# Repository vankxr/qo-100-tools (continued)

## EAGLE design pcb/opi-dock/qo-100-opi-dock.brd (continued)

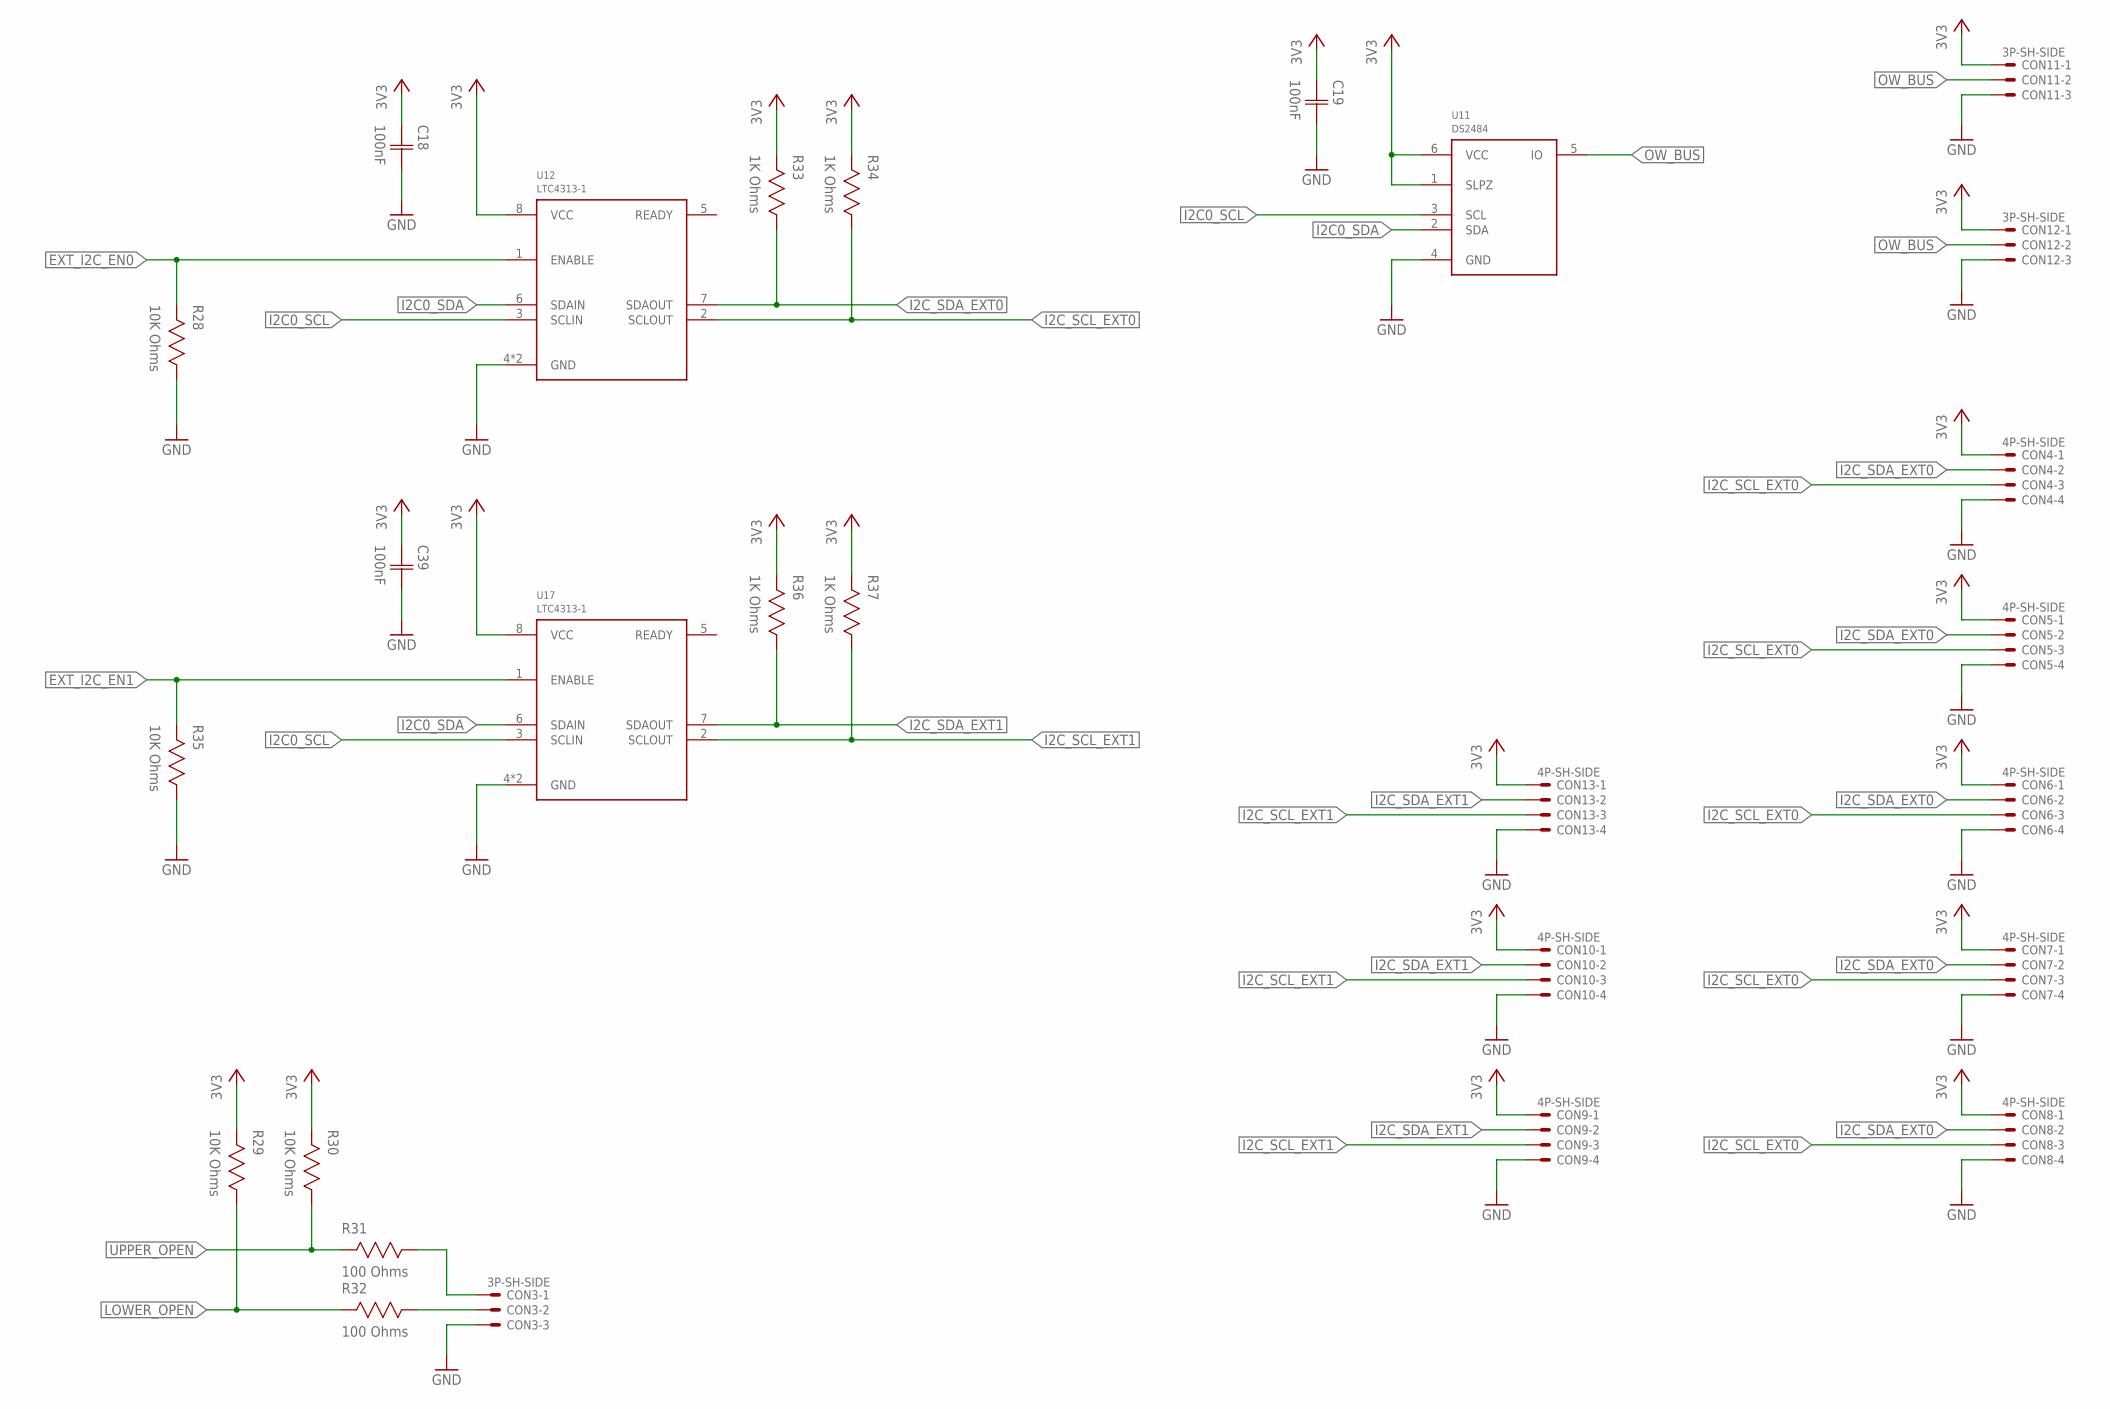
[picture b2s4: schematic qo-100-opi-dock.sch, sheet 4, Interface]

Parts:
C18, C19, C39: 100nF; CAP0603
CON3, CON11, CON12: 3P-SH-SIDE; SH-03-SIDE
CON4, CON5, CON6, CON7, CON8, CON9, CON10, CON13: 4P-SH-SIDE; SH-04-SIDE
R28, R29, R30, R35: 10K Ohms; RES0603
R31, R32: 100 Ohms; RES0603
R33, R34, R36, R37: 1K Ohms; RES0603
U11: DS2484; SOT23-6
U12, U17: LTC4313-1; DFN8

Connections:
3V3: C18.1 (C1), C19.1 (C1), C39.1 (C1), CON4.1, CON5.1, CON6.1, CON7.1, CON8.1, CON9.1, CON10.1, CON11.1, CON12.1, CON13.1, R29.2, R30.2, R33.2, R34.2, R36.2, R37.2, U11.1 (SLPZ), U11.6 (VCC), U12.8 (VCC), U17.8 (VCC); also elsewhere on the board
EXT_I2C_EN0: R28.2, U12.1 (ENABLE); also elsewhere on the board
EXT_I2C_EN1: R35.2, U17.1 (ENABLE); also elsewhere on the board
GND: C18.2 (C2), C19.2 (C2), C39.2 (C2), CON3.3, CON4.4, CON5.4, CON6.4, CON7.4, CON8.4, CON9.4, CON10.4, CON11.3, CON12.3, CON13.4, R28.1, R35.1, U11.4 (GND), U12.4 (GND), U12.9 (GND), U17.4 (GND), U17.9 (GND); also elsewhere on the board
I2C0_SCL: U11.3 (SCL), U12.3 (SCLIN), U17.3 (SCLIN); also elsewhere on the board
I2C0_SDA: U11.2 (SDA), U12.6 (SDAIN), U17.6 (SDAIN); also elsewhere on the board
I2C_SCL_EXT0: CON4.3, CON5.3, CON6.3, CON7.3, CON8.3, R34.1, U12.2 (SCLOUT)
I2C_SCL_EXT1: CON9.3, CON10.3, CON13.3, R37.1, U17.2 (SCLOUT)
I2C_SDA_EXT0: CON4.2, CON5.2, CON6.2, CON7.2, CON8.2, R33.1, U12.7 (SDAOUT)
I2C_SDA_EXT1: CON9.2, CON10.2, CON13.2, R36.1, U17.7 (SDAOUT)
LOWER_OPEN: R29.1, R32.2; also elsewhere on the board
unnamed: CON3.2, R32.1
unnamed: CON3.1, R31.1
OW_BUS: CON11.2, CON12.2, U11.5 (IO)
UPPER_OPEN: R30.1, R31.2; also elsewhere on the board

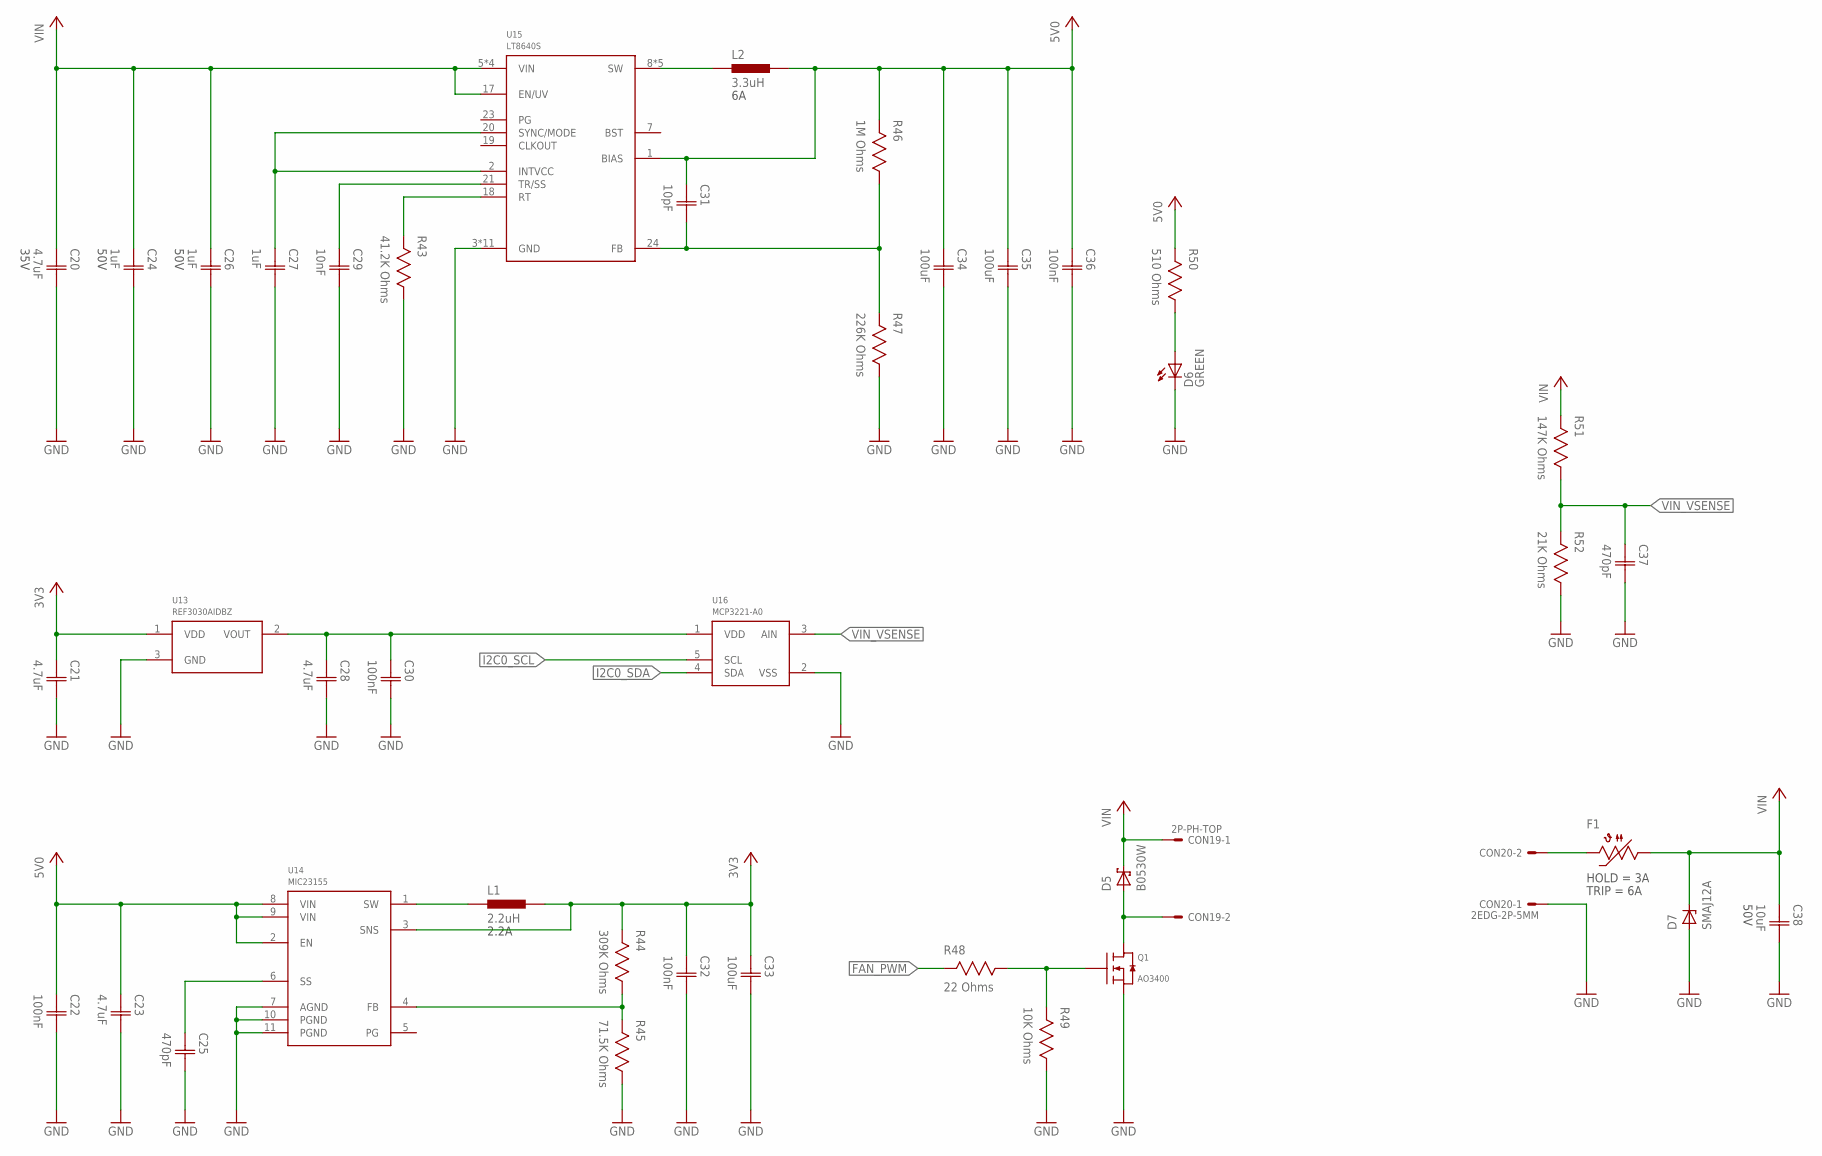
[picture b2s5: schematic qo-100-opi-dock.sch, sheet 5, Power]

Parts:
C20: 4.7uF; CAP0603; VOLTAGE 35V
C21, C23, C28: 4.7uF; CAP0603
C22, C30, C32, C36: 100nF; CAP0603
C24, C26: 1uF; CAP0603; VOLTAGE 50V
C25, C37: 470pF; CAP0603
C27: 1uF; CAP0603
C29: 10nF; CAP0603
C31: 10pF; CAP0603
C33, C34, C35: 100uF; CAP1206
C38: 10uF; CAP1206; VOLTAGE 50V
CON19: 2P-PH-TOP; PH-02-TOP
CON20: 2EDG-2P-5MM
D5: B0530W; SOD-123
D6: LED0603; 0603
D7: SMAJ12A; DO214AC
F1: 2.6A Hold; 1206
L1: 2.2uH; IND2520
L2: 3.3uH; IND0606
Q1: AO3400; SOT23
R43: 41.2K Ohms; RES0603
R44: 309K Ohms; RES0603
R45: 71.5K Ohms; RES0603
R46: 1M Ohms; RES0603
R47: 226K Ohms; RES0603
R48: 22 Ohms; RES0603
R49: 10K Ohms; RES0603
R50: 510 Ohms; RES0603
R51: 147K Ohms; RES0603
R52: 21K Ohms; RES0603
U13: REF3030AIDBZ; SOT23
U14: MIC23155; DFN10
U15: LT8640S; QFN24_CORNER
U16: MCP3221-A0; SOT23-5

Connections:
3V0_ADC_CLEAN: C28.1 (C1), C30.1 (C1), U13.2 (VOUT), U16.1 (VDD)
3V3: C21.1 (C1), C32.1 (C1), C33.1 (C1), L1.2, R44.2, U13.1 (VDD), U14.3 (SNS); also elsewhere on the board
3V3_FB: R44.1, R45.2, U14.4 (FB)
3V3_SOFTSTART: C25.1 (C1), U14.6 (SS)
3V3_SW: L1.1, U14.1 (SW)
5V0: C22.1 (C1), C23.1 (C1), C31.1 (C1), C34.1 (C1), C35.1 (C1), C36.1 (C1), L2.2, R46.2, R50.2, U14.2 (EN), U14.8 (VIN), U14.9 (VIN), U15.1 (BIAS); also elsewhere on the board
5V0_FB: C31.2 (C2), R46.1, R47.2, U15.24 (FB)
5V0_INTVCC: C27.1 (C1), U15.2 (INTVCC), U15.20 (SYNC/MODE)
5V0_RT: R43.2, U15.18 (RT)
5V0_SS: C29.1 (C1), U15.21 (TR/SS)
5V0_SW: L2.1, U15.8 (SW), U15.9 (SW), U15.10 (SW), U15.11 (SW), U15.12 (SW)
FAN_PWM: R48.2; also elsewhere on the board
GND: C20.2 (C2), C21.2 (C2), C22.2 (C2), C23.2 (C2), C24.2 (C2), C25.2 (C2), C26.2 (C2), C27.2 (C2), C28.2 (C2), C29.2 (C2), C30.2 (C2), C32.2 (C2), C33.2 (C2), C34.2 (C2), C35.2 (C2), C36.2 (C2), C37.2 (C2), C38.2 (C2), CON20.P$1, D6.C, D7.A, Q1.2 (S), R43.1, R45.1, R47.1, R49.1, R52.1, U13.3 (GND), U14.7 (AGND), U14.10 (PGND), U14.11 (PGND), U15.3 (GND), U15.16 (GND), U15.22 (GND), U15.25 (GND), U15.26 (GND), U15.27 (GND), U15.28 (GND), U15.29 (GND), U15.30 (GND), U15.31 (GND), U15.32 (GND), U16.2 (VSS); also elsewhere on the board
I2C0_SCL: U16.5 (SCL); also elsewhere on the board
I2C0_SDA: U16.4 (SDA); also elsewhere on the board
unnamed: CON20.P$2, F1.2
unnamed: CON19.2, D5.A, Q1.3 (D)
unnamed: Q1.1 (G), R48.1, R49.2
unnamed: D6.A, R50.1
VIN: C20.1 (C1), C24.1 (C1), C26.1 (C1), C38.1 (C1), CON19.1, D5.C, D7.C, F1.1, R51.2, U15.5 (VIN), U15.6 (VIN), U15.13 (VIN), U15.14 (VIN), U15.17 (EN/UV)
VIN_VSENSE: C37.1 (C1), R51.1, R52.2, U16.3 (AIN)

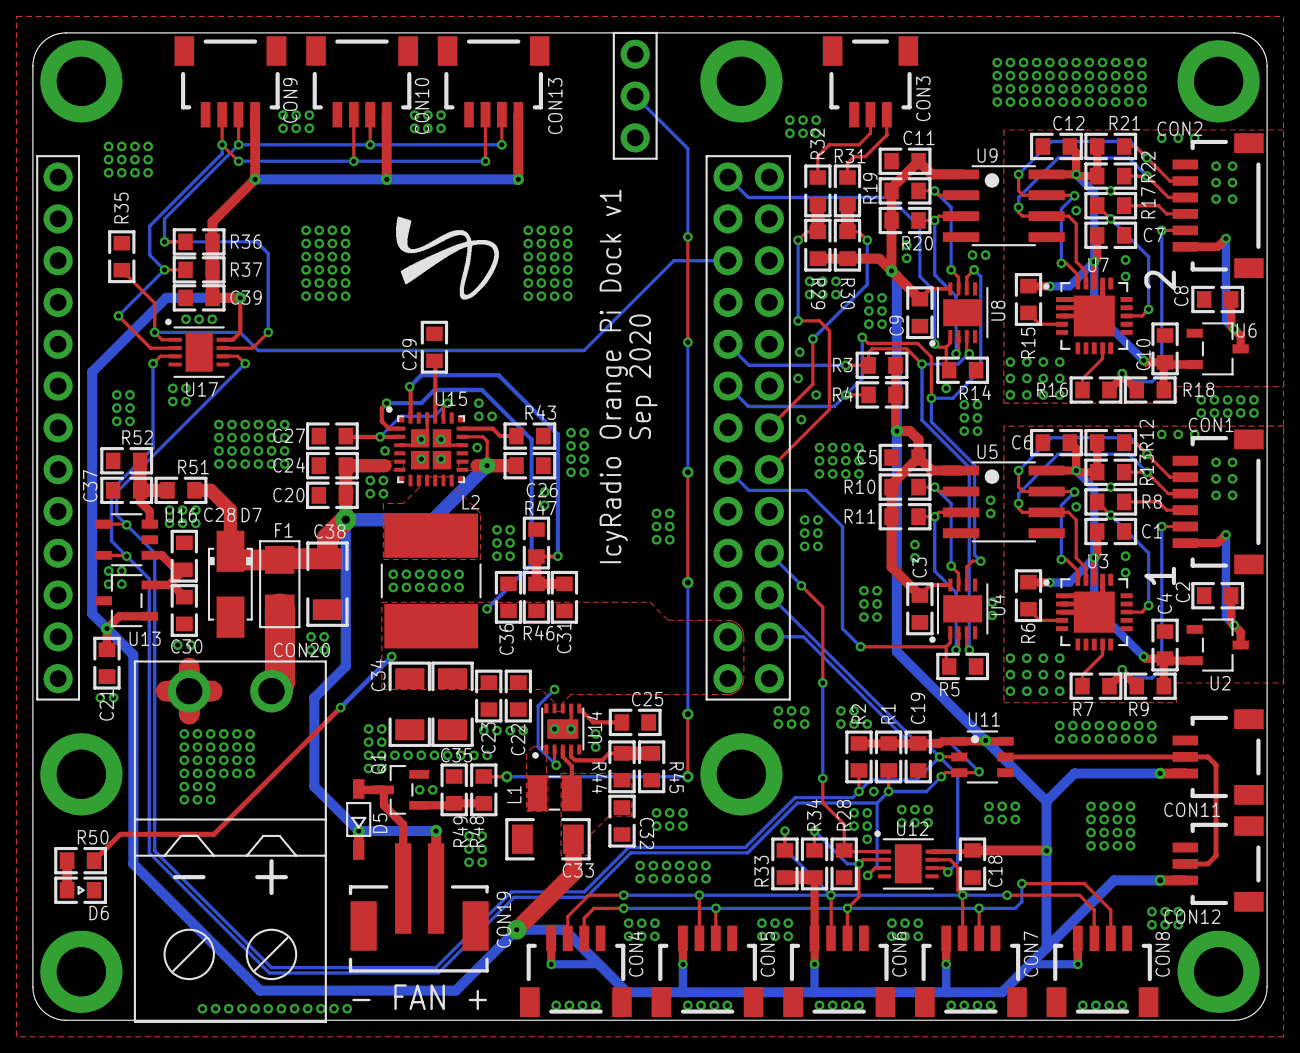
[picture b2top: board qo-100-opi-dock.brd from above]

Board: 2 copper layers, 75.0 x 60.0 mm, 115 parts (0 on the bottom side), 60 nets.

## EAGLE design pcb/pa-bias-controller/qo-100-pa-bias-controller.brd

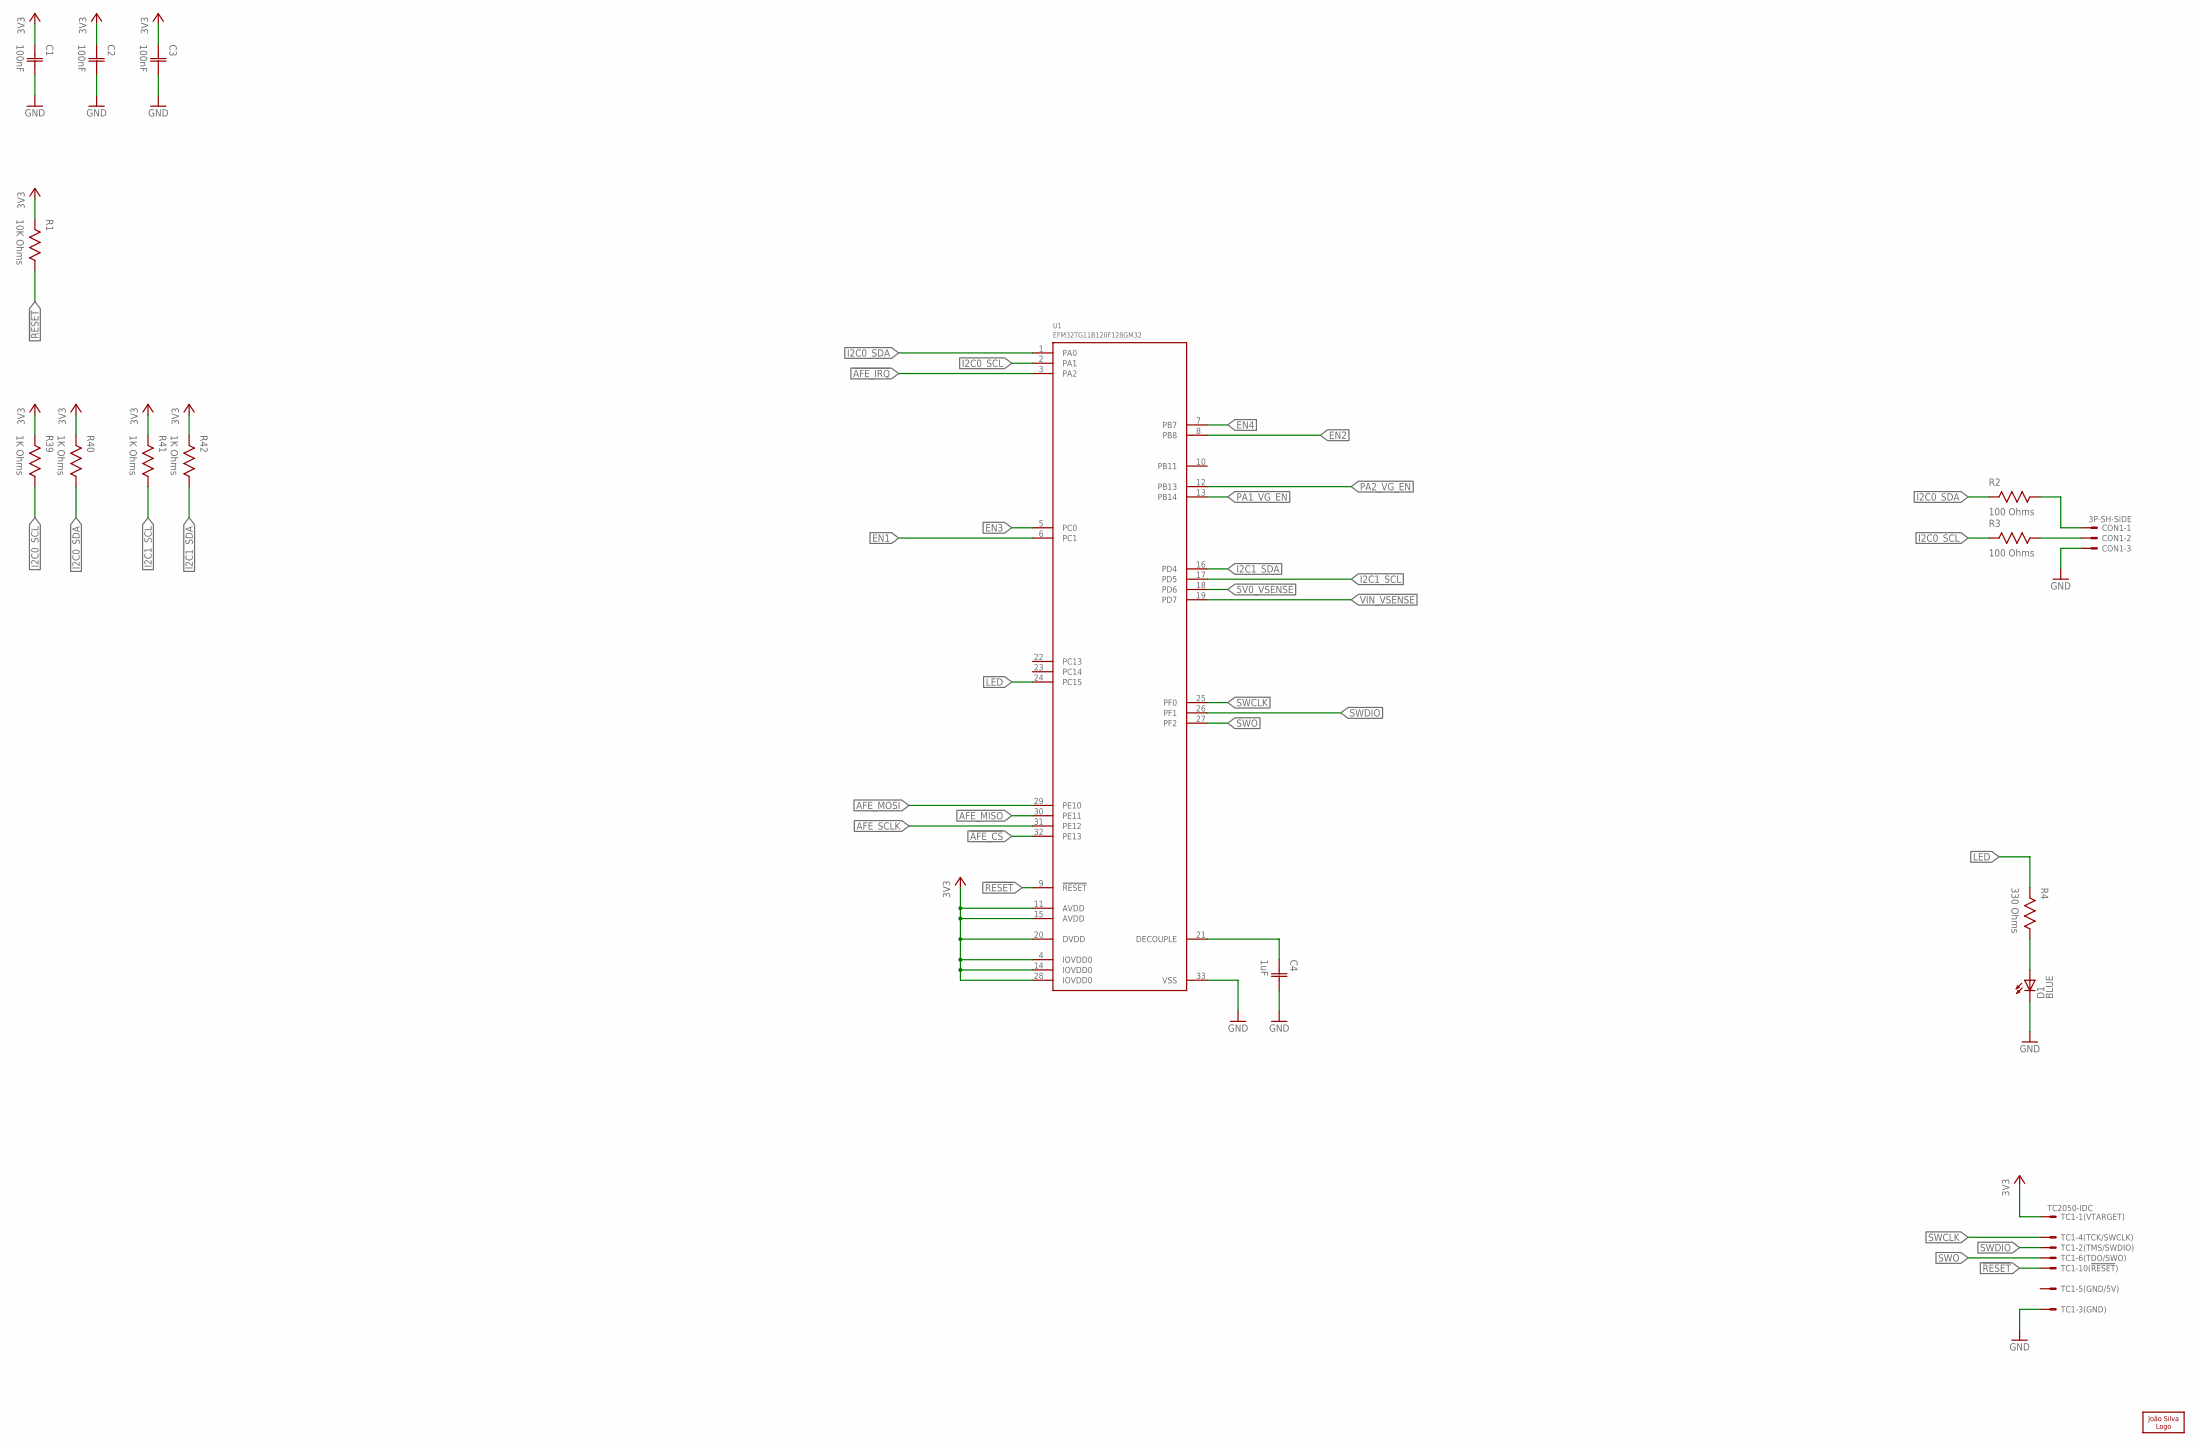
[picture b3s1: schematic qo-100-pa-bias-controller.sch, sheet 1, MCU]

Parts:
C1, C2, C3: 100nF; CAP0603
C4: 1uF; CAP0603
CON1: 3P-SH-SIDE; SH-03-SIDE
D1: LED0603; 0603
LOGO1: JS-10MM; JS_10MM
R1: 10K Ohms; RES0603
R2, R3: 100 Ohms; RES0603
R4: 330 Ohms; RES0603
R39, R40, R41, R42: 1K Ohms; RES0603
TC1: TC2050-IDC
U1: EFM32TG11B120F128GM32; QFN32_0.5P_TG

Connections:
3V3: C1.1 (C1), C2.1 (C1), C3.1 (C1), R1.2, R39.2, R40.2, R41.2, R42.2, TC1.1, U1.4 (IOVDD0), U1.11 (AVDD), U1.14 (IOVDD0), U1.15 (AVDD), U1.20 (DVDD), U1.28 (IOVDD0); also elsewhere on the board
5V0_VSENSE: U1.18 (PD6); also elsewhere on the board
!AFE_CS: U1.32 (PE13); also elsewhere on the board
!AFE_IRQ: U1.3 (PA2); also elsewhere on the board
!RESET: R1.1, TC1.10, U1.9 (!RESET)
AFE_MISO: U1.30 (PE11); also elsewhere on the board
AFE_MOSI: U1.29 (PE10); also elsewhere on the board
AFE_SCLK: U1.31 (PE12); also elsewhere on the board
EN1: U1.6 (PC1); also elsewhere on the board
EN2: U1.8 (PB8); also elsewhere on the board
EN3: U1.5 (PC0); also elsewhere on the board
EN4: U1.7 (PB7); also elsewhere on the board
GND: C1.2 (C2), C2.2 (C2), C3.2 (C2), C4.2 (C2), CON1.3, D1.C, TC1.3, U1.33 (VSS); also elsewhere on the board
I2C0_SCL: R3.2, R39.1, U1.2 (PA1)
I2C0_SDA: R2.2, R40.1, U1.1 (PA0)
I2C1_SCL: R41.1, U1.17 (PD5); also elsewhere on the board
I2C1_SDA: R42.1, U1.16 (PD4); also elsewhere on the board
LED: R4.2, U1.24 (PC15)
unnamed: CON1.2, R3.1
unnamed: C4.1 (C1), U1.21 (DECOUPLE)
unnamed: D1.A, R4.1
unnamed: CON1.1, R2.1
PA1_VG_EN: U1.13 (PB14); also elsewhere on the board
PA2_VG_EN: U1.12 (PB13); also elsewhere on the board
SWCLK: TC1.4, U1.25 (PF0)
SWDIO: TC1.2, U1.26 (PF1)
SWO: TC1.6, U1.27 (PF2)
VIN_VSENSE: U1.19 (PD7); also elsewhere on the board

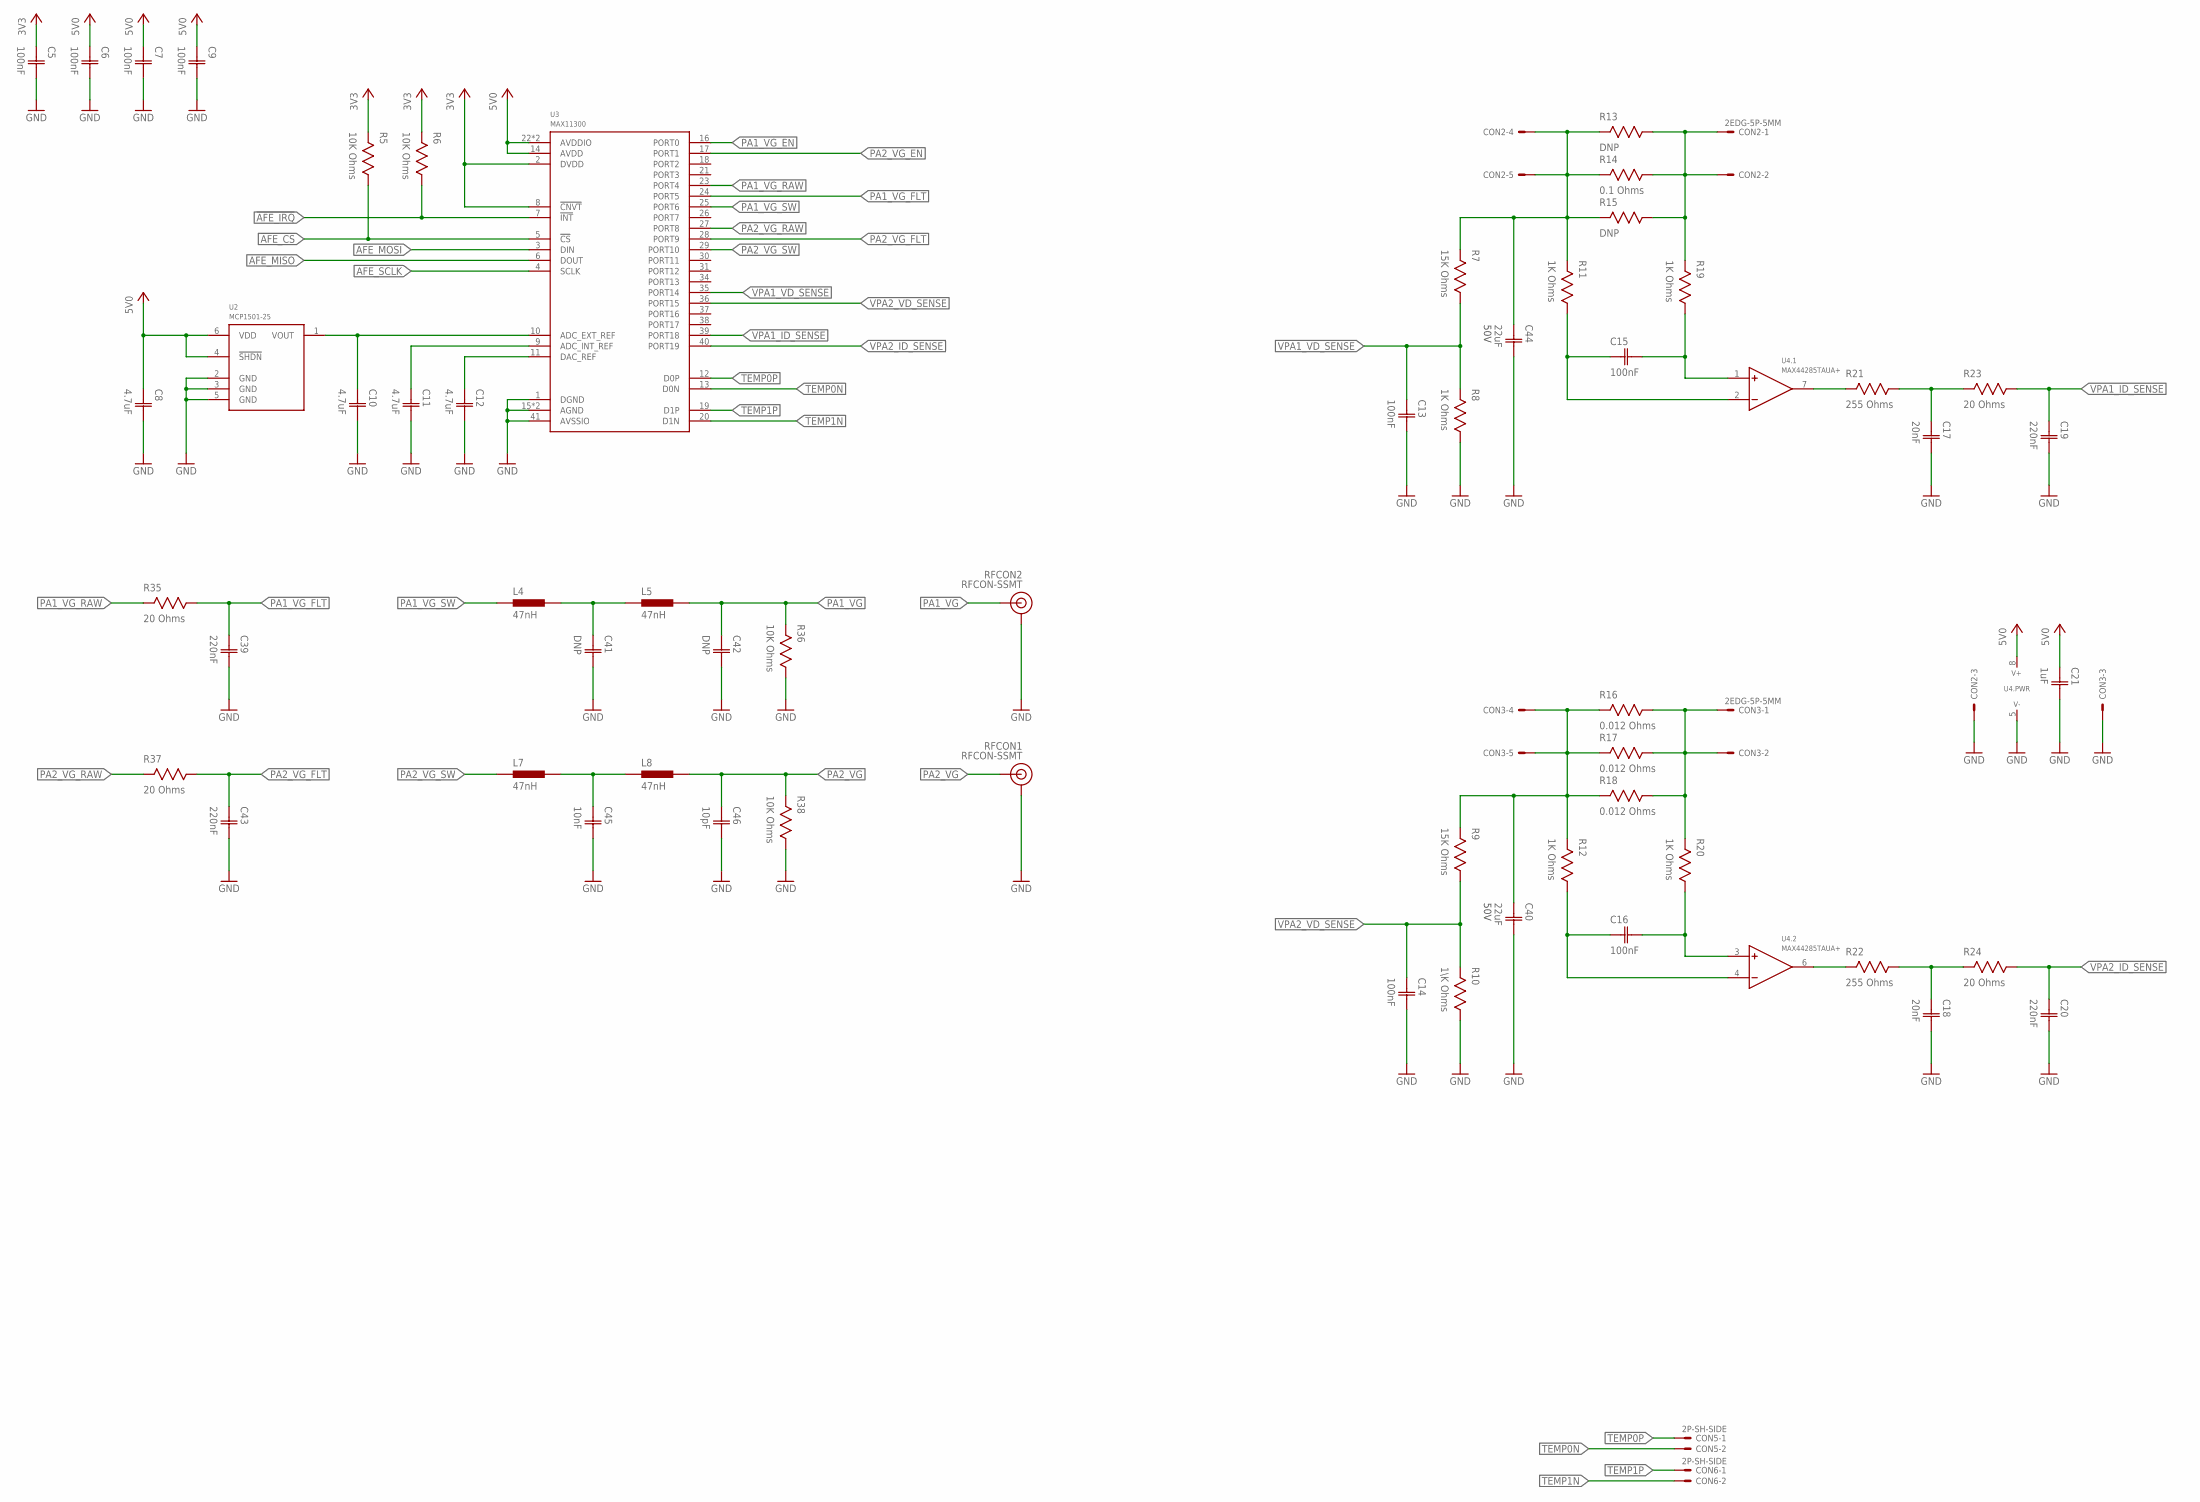
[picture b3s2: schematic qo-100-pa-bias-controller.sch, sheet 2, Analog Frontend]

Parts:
C5, C6, C7, C9, C13, C14, C15, C16: 100nF; CAP0603
C8, C10, C11, C12: 4.7uF; CAP0603
C17, C18: 20nF; CAP0603
C19, C20, C39, C43: 220nF; CAP0603
C21: 1uF; CAP0603
C40, C44: 22uF; CAP2220; VOLTAGE 50V
C41, C42: DNP; CAP0603
C45: 10nF; CAP0603
C46: 10pF; CAP0603
CON2, CON3: 2EDG-5P-5MM
CON5, CON6: 2P-SH-SIDE; SH-02-SIDE
L4, L5, L7, L8: 47nH; IND0603
R5, R6, R36, R38: 10K Ohms; RES0603
R7, R9: 15K Ohms; RES0603
R8, R11, R12, R19, R20: 1K Ohms; RES0603
R10: 1\K Ohms; RES0603
R13, R15: DNP; RES2512
R14: 0.1 Ohms; RES2512
R16, R17, R18: 0.012 Ohms; RES2512
R21, R22: 255 Ohms; RES0603
R23, R24, R35, R37: 20 Ohms; RES0603
RFCON1, RFCON2: RFCON-SSMT; SSMT
U2: MCP1501-25; SOT23-6
U3: MAX11300; QFN40
U4: MAX44285TAUA+; MSOP8

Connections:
3V3: C5.1 (C1), R5.2, R6.2, U3.2 (DVDD), U3.8 (!CNVT); also elsewhere on the board
5V0: C6.1 (C1), C7.1 (C1), C8.1 (C1), C9.1 (C1), C21.1 (C1), U2.4 (!SHDN), U2.6 (VDD), U3.14 (AVDD), U3.22 (AVDDIO), U3.33 (AVDDIO), U4.8 (V+); also elsewhere on the board
!AFE_CS: R5.1, U3.5 (!CS); also elsewhere on the board
!AFE_IRQ: R6.1, U3.7 (!INT); also elsewhere on the board
AFE_ADC_EXT_REF: C10.1 (C1), U2.1 (VOUT), U3.10 (ADC_EXT_REF)
AFE_ADC_INT_REF: C11.1 (C1), U3.9 (ADC_INT_REF)
AFE_DAC_REF: C12.1 (C1), U3.11 (DAC_REF)
AFE_MISO: U3.6 (DOUT); also elsewhere on the board
AFE_MOSI: U3.3 (DIN); also elsewhere on the board
AFE_SCLK: U3.4 (SCLK); also elsewhere on the board
GND: C5.2 (C2), C6.2 (C2), C7.2 (C2), C8.2 (C2), C9.2 (C2), C10.2 (C2), C11.2 (C2), C12.2 (C2), C13.2 (C2), C14.2 (C2), C17.2 (C2), C18.2 (C2), C19.2 (C2), C20.2 (C2), C21.2 (C2), C39.2 (C2), C40.2 (C2), C41.2 (C2), C42.2 (C2), C43.2 (C2), C44.2 (C2), C45.2 (C2), C46.2 (C2), CON2.P$3, CON3.P$3, R8.1, R10.1, R36.1, R38.1, RFCON1.1 (GND), RFCON1.3 (GND), RFCON1.4 (GND), RFCON2.1 (GND), RFCON2.3 (GND), RFCON2.4 (GND), U2.2 (GND), U2.3 (GND), U2.5 (GND), U3.1 (DGND), U3.15 (AGND), U3.32 (AGND), U3.41 (AVSSIO), U4.5 (V-); also elsewhere on the board
unnamed: R22.2, U4.6 (OUT)
unnamed: C18.1 (C1), R22.1, R24.2
unnamed: R21.2, U4.7 (OUT)
unnamed: C17.1 (C1), R21.1, R23.2
unnamed: C41.1 (C1), L4.2, L5.1
unnamed: C45.1 (C1), L7.2, L8.1
PA1_VD_IN: CON2.P$1, CON2.P$2, R13.1, R14.1, R15.1, R19.2
PA1_VD_OUT: C44.1 (C1), CON2.P$4, CON2.P$5, R7.2, R11.2, R13.2, R14.2, R15.2
PA1_VG: C42.1 (C1), L5.2, R36.2, RFCON2.2 (SIGNAL)
PA1_VG_EN: U3.16 (PORT0); also elsewhere on the board
PA1_VG_FLT: C39.1 (C1), R35.1, U3.24 (PORT5)
PA1_VG_RAW: R35.2, U3.23 (PORT4)
PA1_VG_SW: L4.1, U3.25 (PORT6)
PA2_VD_IN: CON3.P$1, CON3.P$2, R16.1, R17.1, R18.1, R20.2
PA2_VD_OUT: C40.1 (C1), CON3.P$4, CON3.P$5, R9.2, R12.2, R16.2, R17.2, R18.2
PA2_VG: C46.1 (C1), L8.2, R38.2, RFCON1.2 (SIGNAL)
PA2_VG_EN: U3.17 (PORT1); also elsewhere on the board
PA2_VG_FLT: C43.1 (C1), R37.1, U3.28 (PORT9)
PA2_VG_RAW: R37.2, U3.27 (PORT8)
PA2_VG_SW: L7.1, U3.29 (PORT10)
TEMP0N: CON5.2, U3.13 (D0N)
TEMP0P: CON5.1, U3.12 (D0P)
TEMP1N: CON6.2, U3.20 (D1N)
TEMP1P: CON6.1, U3.19 (D1P)
VPA1_ID_SENSE: C19.1 (C1), R23.1, U3.39 (PORT18)
VPA1_ID_SENSE_N: C15.1 (C1), R11.1, U4.2 (-IN)
VPA1_ID_SENSE_P: C15.2 (C2), R19.1, U4.1 (+IN)
VPA1_VD_SENSE: C13.1 (C1), R7.1, R8.2, U3.35 (PORT14)
VPA2_ID_SENSE: C20.1 (C1), R24.1, U3.40 (PORT19)
VPA2_ID_SENSE_N: C16.1 (C1), R12.1, U4.4 (-IN)
VPA2_ID_SENSE_P: C16.2 (C2), R20.1, U4.3 (+IN)
VPA2_VD_SENSE: C14.1 (C1), R9.1, R10.2, U3.36 (PORT15)
